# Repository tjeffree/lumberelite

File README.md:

# lumberelite

Based off of the brilliant work of [Peej's Lumberjack](https://github.com/peej/lumberjack-keyboard).

An Elite-C version of the Lumberjack with the addition of an OLED screen.

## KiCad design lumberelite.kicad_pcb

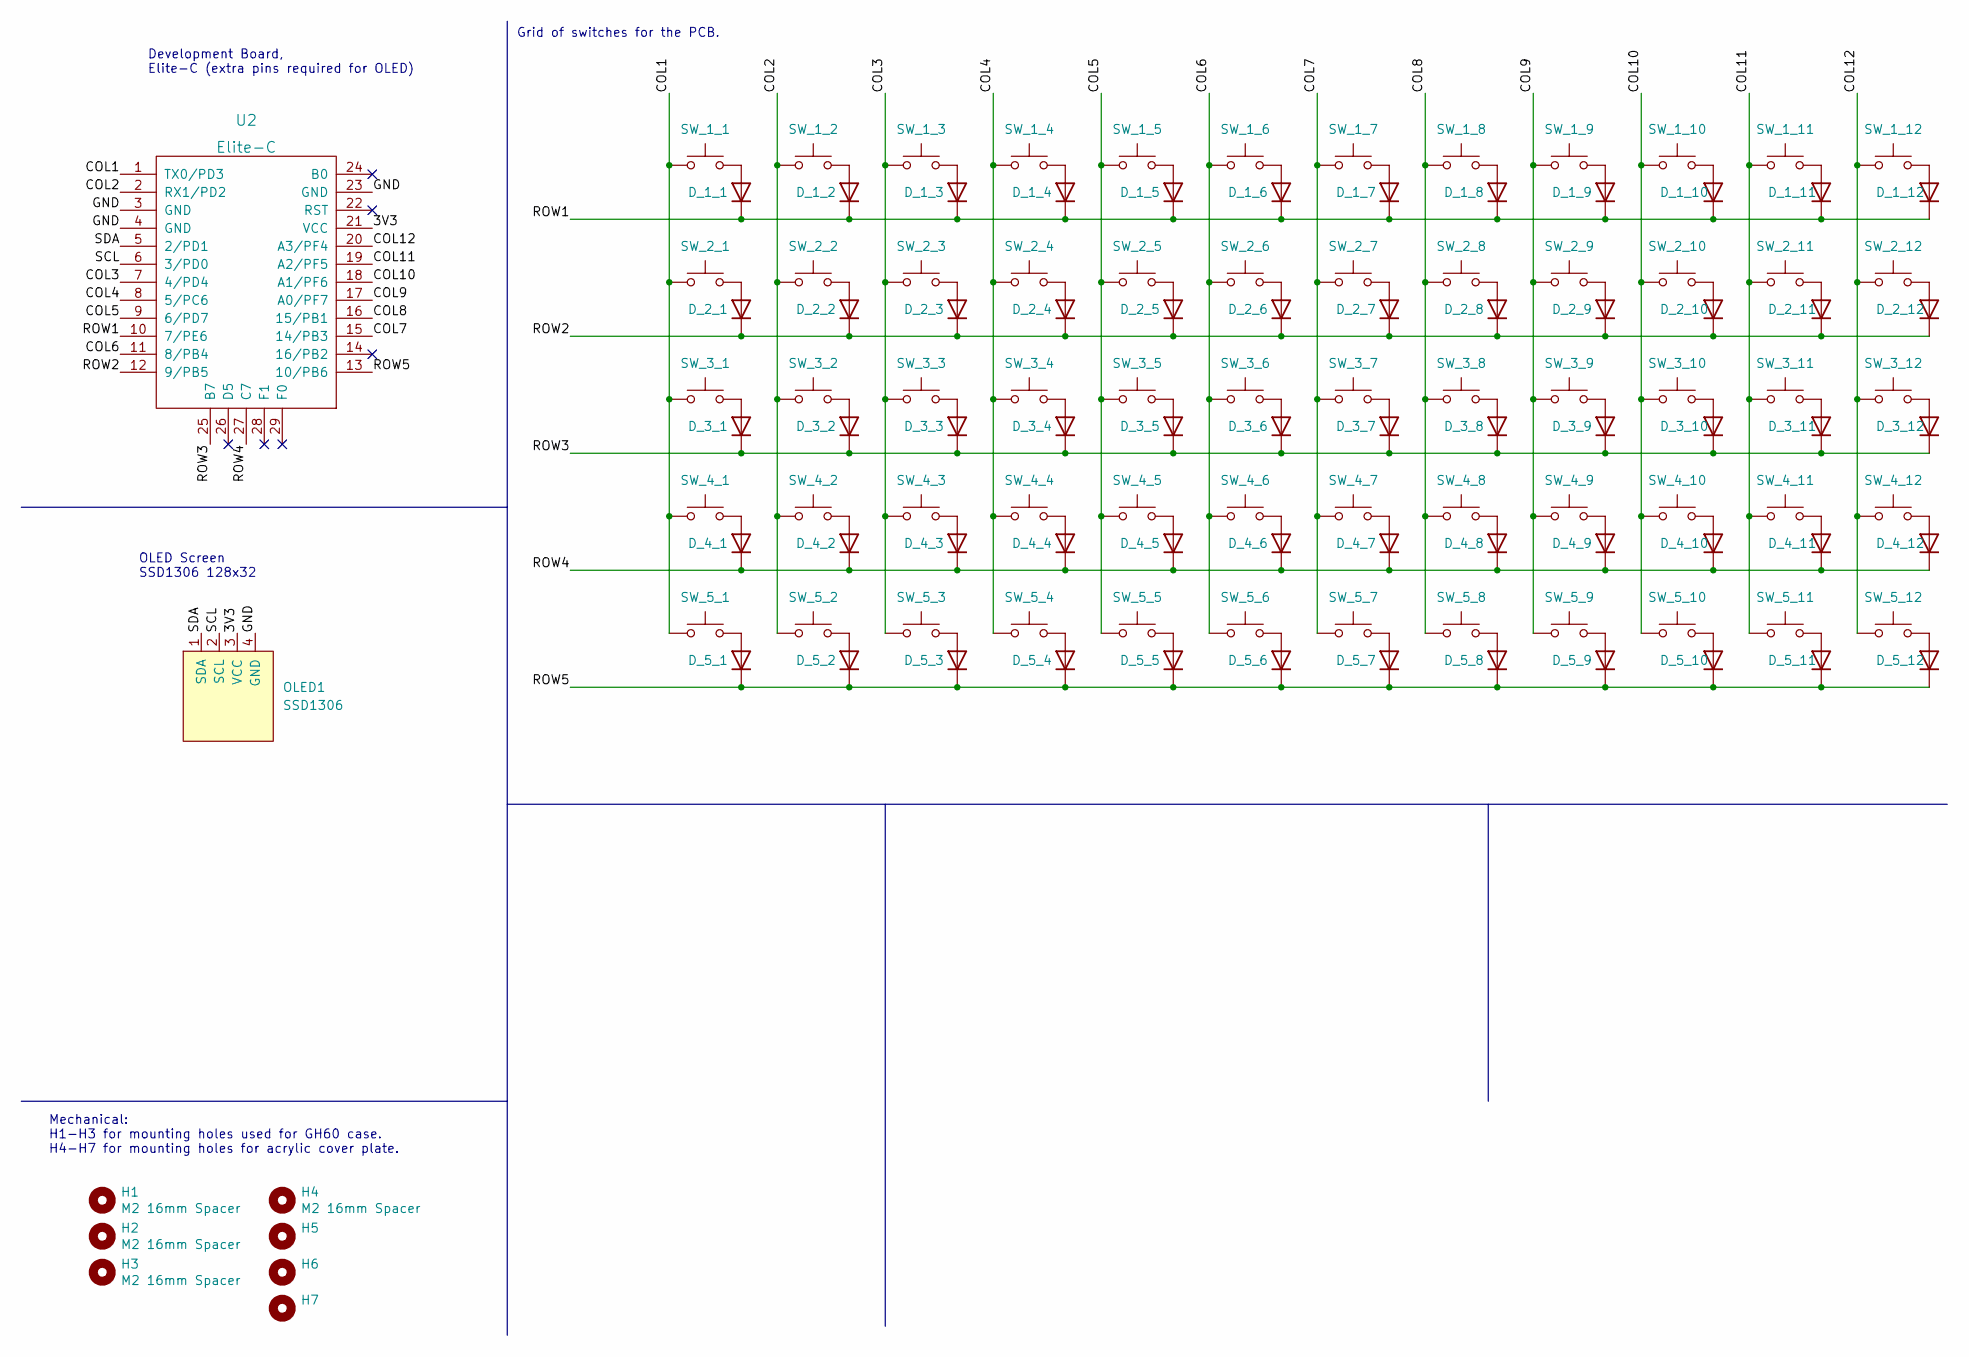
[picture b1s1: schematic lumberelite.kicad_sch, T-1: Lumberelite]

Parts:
D_1_1, D_1_2, D_1_3, D_1_4, D_1_5, D_1_6, D_1_7, D_1_8, D_1_9, D_1_10, D_1_11, D_1_12, D_2_1, D_2_2, D_2_3, D_2_4, D_2_5, D_2_6, D_2_7, D_2_8, D_2_9, D_2_10, D_2_11, D_2_12, D_3_1, D_3_2, D_3_3, D_3_4, D_3_5, D_3_6, D_3_7, D_3_8, D_3_9, D_3_10, D_3_11, D_3_12, D_4_1, D_4_2, D_4_3, D_4_4, D_4_5, D_4_6, D_4_7, D_4_8, D_4_9, D_4_10, D_4_11, D_4_12, D_5_1, D_5_2, D_5_3, D_5_4, D_5_5, D_5_6, D_5_7, D_5_8, D_5_9, D_5_10, D_5_11, D_5_12: 1N4148; Diode-dual
H1, H2, H3, H4: M2 16mm Spacer; MountingHole_2.2mm_M2_DIN965_Pad
H5: Bumpon_3M_F0502
H6, H7: MountingHole_2.2mm_M2_elongated
OLED1: SSD1306; OLED_v2
SW_1_1, SW_1_2, SW_1_3, SW_1_4, SW_1_5, SW_1_6, SW_1_7, SW_1_8, SW_1_9, SW_1_10, SW_1_11, SW_1_12, SW_2_1, SW_2_2, SW_2_3, SW_2_4, SW_2_5, SW_2_6, SW_2_7, SW_2_8, SW_2_9, SW_2_10, SW_2_11, SW_2_12, SW_3_1, SW_3_2, SW_3_3, SW_3_4, SW_3_5, SW_3_6, SW_3_7, SW_3_8, SW_3_9, SW_3_10, SW_3_11, SW_3_12, SW_4_1, SW_4_2, SW_4_3, SW_4_4, SW_4_5, SW_4_6, SW_4_7, SW_4_8, SW_4_9, SW_4_10, SW_4_11, SW_4_12, SW_5_1, SW_5_2, SW_5_3, SW_5_4, SW_5_5, SW_5_6, SW_5_7, SW_5_8, SW_5_9, SW_5_10, SW_5_11, SW_5_12: MX-compatible or Kailh Choc v1; SW_MX_PG1350_NoLed
U2: Elite-C; Elite-C-ZigZag

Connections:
/3V3: OLED1.3 (VCC), U2.21 (VCC)
/COL1: SW_1_1.1, SW_2_1.1, SW_3_1.1, SW_4_1.1, SW_5_1.1, U2.1 (TX0/PD3)
/COL2: SW_1_2.1, SW_2_2.1, SW_3_2.1, SW_4_2.1, SW_5_2.1, U2.2 (RX1/PD2)
/COL3: SW_1_3.1, SW_2_3.1, SW_3_3.1, SW_4_3.1, SW_5_3.1, U2.7 (4/PD4)
/COL4: SW_1_4.1, SW_2_4.1, SW_3_4.1, SW_4_4.1, SW_5_4.1, U2.8 (5/PC6)
/COL5: SW_1_5.1, SW_2_5.1, SW_3_5.1, SW_4_5.1, SW_5_5.1, U2.9 (6/PD7)
/COL6: SW_1_6.1, SW_2_6.1, SW_3_6.1, SW_4_6.1, SW_5_6.1, U2.11 (8/PB4)
/COL7: SW_1_7.1, SW_2_7.1, SW_3_7.1, SW_4_7.1, SW_5_7.1, U2.15 (14/PB3)
/COL8: SW_1_8.1, SW_2_8.1, SW_3_8.1, SW_4_8.1, SW_5_8.1, U2.16 (15/PB1)
/COL9: SW_1_9.1, SW_2_9.1, SW_3_9.1, SW_4_9.1, SW_5_9.1, U2.17 (A0/PF7)
/COL10: SW_1_10.1, SW_2_10.1, SW_3_10.1, SW_4_10.1, SW_5_10.1, U2.18 (A1/PF6)
/COL11: SW_1_11.1, SW_2_11.1, SW_3_11.1, SW_4_11.1, SW_5_11.1, U2.19 (A2/PF5)
/COL12: SW_1_12.1, SW_2_12.1, SW_3_12.1, SW_4_12.1, SW_5_12.1, U2.20 (A3/PF4)
/GND: OLED1.4 (GND), U2.3 (GND), U2.4 (GND), U2.23 (GND)
/ROW1: D_1_1.1 (K), D_1_2.1 (K), D_1_3.1 (K), D_1_4.1 (K), D_1_5.1 (K), D_1_6.1 (K), D_1_7.1 (K), D_1_8.1 (K), D_1_9.1 (K), D_1_10.1 (K), D_1_11.1 (K), D_1_12.1 (K), U2.10 (7/PE6)
/ROW2: D_2_1.1 (K), D_2_2.1 (K), D_2_3.1 (K), D_2_4.1 (K), D_2_5.1 (K), D_2_6.1 (K), D_2_7.1 (K), D_2_8.1 (K), D_2_9.1 (K), D_2_10.1 (K), D_2_11.1 (K), D_2_12.1 (K), U2.12 (9/PB5)
/ROW3: D_3_1.1 (K), D_3_2.1 (K), D_3_3.1 (K), D_3_4.1 (K), D_3_5.1 (K), D_3_6.1 (K), D_3_7.1 (K), D_3_8.1 (K), D_3_9.1 (K), D_3_10.1 (K), D_3_11.1 (K), D_3_12.1 (K), U2.25 (B7)
/ROW4: D_4_1.1 (K), D_4_2.1 (K), D_4_3.1 (K), D_4_4.1 (K), D_4_5.1 (K), D_4_6.1 (K), D_4_7.1 (K), D_4_8.1 (K), D_4_9.1 (K), D_4_10.1 (K), D_4_11.1 (K), D_4_12.1 (K), U2.27 (C7)
/ROW5: D_5_1.1 (K), D_5_2.1 (K), D_5_3.1 (K), D_5_4.1 (K), D_5_5.1 (K), D_5_6.1 (K), D_5_7.1 (K), D_5_8.1 (K), D_5_9.1 (K), D_5_10.1 (K), D_5_11.1 (K), D_5_12.1 (K), U2.13 (10/PB6)
/SCL: OLED1.2 (SCL), U2.6 (3/PD0)
/SDA: OLED1.1 (SDA), U2.5 (2/PD1)
unnamed: D_1_1.2 (A), SW_1_1.2
unnamed: D_1_2.2 (A), SW_1_2.2
unnamed: D_1_3.2 (A), SW_1_3.2
unnamed: D_1_4.2 (A), SW_1_4.2
unnamed: D_1_5.2 (A), SW_1_5.2
unnamed: D_1_6.2 (A), SW_1_6.2
unnamed: D_1_7.2 (A), SW_1_7.2
unnamed: D_1_8.2 (A), SW_1_8.2
unnamed: D_1_9.2 (A), SW_1_9.2
unnamed: D_1_10.2 (A), SW_1_10.2
unnamed: D_1_11.2 (A), SW_1_11.2
unnamed: D_1_12.2 (A), SW_1_12.2
unnamed: D_2_1.2 (A), SW_2_1.2
unnamed: D_2_2.2 (A), SW_2_2.2
unnamed: D_2_3.2 (A), SW_2_3.2
unnamed: D_2_4.2 (A), SW_2_4.2
unnamed: D_2_5.2 (A), SW_2_5.2
unnamed: D_2_6.2 (A), SW_2_6.2
unnamed: D_2_7.2 (A), SW_2_7.2
unnamed: D_2_8.2 (A), SW_2_8.2
unnamed: D_2_9.2 (A), SW_2_9.2
unnamed: D_2_10.2 (A), SW_2_10.2
unnamed: D_2_11.2 (A), SW_2_11.2
unnamed: D_2_12.2 (A), SW_2_12.2
unnamed: D_3_1.2 (A), SW_3_1.2
unnamed: D_3_2.2 (A), SW_3_2.2
unnamed: D_3_3.2 (A), SW_3_3.2
unnamed: D_3_4.2 (A), SW_3_4.2
unnamed: D_3_5.2 (A), SW_3_5.2
unnamed: D_3_6.2 (A), SW_3_6.2
unnamed: D_3_7.2 (A), SW_3_7.2
unnamed: D_3_8.2 (A), SW_3_8.2
unnamed: D_3_9.2 (A), SW_3_9.2
unnamed: D_3_10.2 (A), SW_3_10.2
unnamed: D_3_11.2 (A), SW_3_11.2
unnamed: D_3_12.2 (A), SW_3_12.2
unnamed: D_4_1.2 (A), SW_4_1.2
unnamed: D_4_2.2 (A), SW_4_2.2
unnamed: D_4_3.2 (A), SW_4_3.2
unnamed: D_4_4.2 (A), SW_4_4.2
unnamed: D_4_5.2 (A), SW_4_5.2
unnamed: D_4_6.2 (A), SW_4_6.2
unnamed: D_4_7.2 (A), SW_4_7.2
unnamed: D_4_8.2 (A), SW_4_8.2
unnamed: D_4_9.2 (A), SW_4_9.2
unnamed: D_4_10.2 (A), SW_4_10.2
unnamed: D_4_11.2 (A), SW_4_11.2
unnamed: D_4_12.2 (A), SW_4_12.2
unnamed: D_5_1.2 (A), SW_5_1.2
unnamed: D_5_2.2 (A), SW_5_2.2
unnamed: D_5_3.2 (A), SW_5_3.2
unnamed: D_5_4.2 (A), SW_5_4.2
unnamed: D_5_5.2 (A), SW_5_5.2
unnamed: D_5_6.2 (A), SW_5_6.2
unnamed: D_5_7.2 (A), SW_5_7.2
unnamed: D_5_8.2 (A), SW_5_8.2
unnamed: D_5_9.2 (A), SW_5_9.2
unnamed: D_5_10.2 (A), SW_5_10.2
unnamed: D_5_11.2 (A), SW_5_11.2
unnamed: D_5_12.2 (A), SW_5_12.2

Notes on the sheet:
Grid of switches for the PCB.
OLED Screen SSD1306 128x32
Development Board, Elite-C (extra pins required for OLED)
Mechanical: H1-H3 for mounting holes used for GH60 case. H4-H7 for mounting holes for acrylic cover plate.

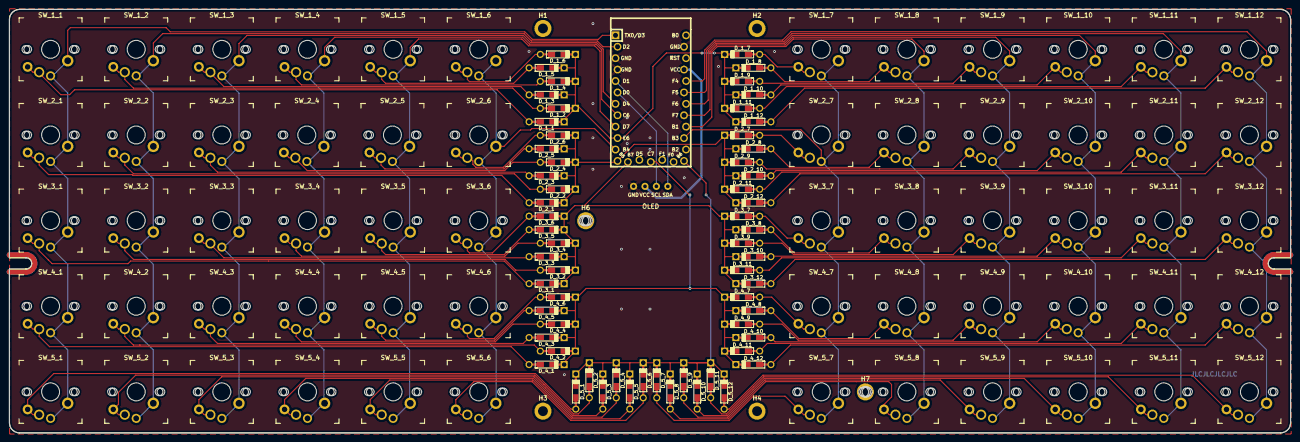
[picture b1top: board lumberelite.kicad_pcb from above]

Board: 2 copper layers, 285.0 x 94.2 mm, 131 parts (0 on the bottom side), 81 nets.

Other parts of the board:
HOLE: Graphic_Mask_HalfHole
HOLE#2: Graphic_Mask_HalfHole

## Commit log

2022-02-27 Add gitignore
2022-02-27 Add qmk config
2022-02-27 Add image
2022-02-27 Update images
2022-06-13 Update qmk version
